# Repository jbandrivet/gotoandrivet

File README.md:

# GotoAndrivet — Contrôleur Multi-Montures OnStep

**Site du projet : [goto-andrivet.duckdns.org](https://goto-andrivet.duckdns.org)**

**Fonctionne sous Linux et sous Windows** : [installation Linux](#installation-en-un-clic-linux) ·
[installation Windows](#installation-windows). La monture et ses firmwares sont les mêmes : une carte
flashée une fois sert avec les deux.

Ce projet supporte de manière universelle trois types de montures astronomiques :
1. **Alt-Azimutale (AltAz)** : Pour montures Dobson et Alt-Azimutales standards.
2. **Fourche Équatoriale (ForkEq)** : Pour montures équatoriales à fourche ou tables équatoriales (aucun retournement de méridien requis, suivi sidéral direct sur l'angle horaire).
3. **Monture Équatoriale Allemande (GermanEq / GEM)** : Pour montures équatoriales allemandes (gestion automatique du **retournement de méridien** et de la position de pilier *Pier Side* Est/Ouest).

---

## Installation en un clic (Linux)

La carte du ciel et GoTo (**GotoAndrivet**) et le **configurateur** s'installent ensemble, avec leurs raccourcis sur le Bureau et dans le menu des applications. L'installateur prend toujours la dernière version du dépôt ; ensuite, le bouton « Mise à jour » des applications suffit.

**Ubuntu et Debian, le plus simple : [⬇ Télécharger GotoAndrivet.deb](https://github.com/jbandrivet/gotoandrivet/releases/latest/download/GotoAndrivet.deb)**

1. Double-cliquez sur le fichier téléchargé : le Centre d'applications s'ouvre. Cliquez sur **Installer** (votre mot de passe est demandé).
2. Ouvrez **GotoAndrivet - Carte du ciel** depuis le menu des applications. La première fois, GotoAndrivet s'installe dans votre dossier personnel (quelques minutes), puis s'ouvre.

**Autres distributions : [⬇ Télécharger l'installateur Linux](https://github.com/jbandrivet/gotoandrivet/releases/latest/download/Install_Goto_Universal)**, puis, dans le dossier Téléchargements :

1. clic droit sur `Install_Goto_Universal` → **Propriétés** → activez **Exécutable comme programme** ;
2. clic droit → **Exécuter comme un programme**, puis « Installer ».

Le double-clic ne lance pas un programme téléchargé : il propose de chercher une application dans le Centre d'applications, qui ne trouve rien. Passez par le clic droit.

Ou en une seule commande, dans un terminal :

```sh
wget -qO- https://raw.githubusercontent.com/jbandrivet/gotoandrivet/main/installer.sh | sh
```

Prérequis pour l'installateur et la commande (le paquet .deb les installe tout seul) : `sudo apt install python3-venv python3-tk`. Pour le module caméra : `sudo apt install astrometry.net astrometry-data-tycho2` et le SDK caméra de ZWO.

**Connexion de la monture** : dans la carte du ciel, laissez le port sur **Auto** et cliquez sur **Connecter**. La carte du ciel essaie d'abord le dernier port qui a marché, puis les cartes Teensy et Arduino, puis les adaptateurs série USB (CH340, FTDI, CP210x, PL2303), et garde celui où la monture répond. Les ports déjà pris (KStars, dérotateur) sont sautés. Si la recherche ne trouve rien, choisissez le port dans la liste, ou tapez-le, par exemple `/dev/ttyACM0`.

---

## Installation (Windows)

Trois `.exe` autonomes, sans installation : copiez-les dans un dossier à vous (Documents, Bureau) et
double-cliquez.

* **[⬇ GotoAndrivet_Carte_du_ciel.exe](https://github.com/jbandrivet/gotoandrivet/releases/download/windows/GotoAndrivet_Carte_du_ciel.exe)** : la carte du ciel et le GoTo
* **[⬇ GotoAndrivet_Configurateur.exe](https://github.com/jbandrivet/gotoandrivet/releases/download/windows/GotoAndrivet_Configurateur.exe)** : le réglage de la monture
* **[⬇ GotoAndrivet_Raquette.exe](https://github.com/jbandrivet/gotoandrivet/releases/download/windows/GotoAndrivet_Raquette.exe)** : la raquette virtuelle

La monture (Arduino Mega, clone ou Teensy) est trouvée toute seule sur son port COM. Si Windows affiche
« Windows a protégé votre ordinateur » : **Informations complémentaires** → **Exécuter quand même** (les
`.exe` ne sont pas signés).

Les `.exe` sont fabriqués par GitHub à chaque modification du programme
([release `windows`](https://github.com/jbandrivet/gotoandrivet/releases/tag/windows)) ; le bouton
« Mise à jour » passe au rouge quand une nouvelle version existe et les remplace d'un clic. Pas
disponibles sous Windows : caméras ZWO, focuseur EAF, astrométrie et guidage. Fabrication : dossier
[`windows/`](windows/LISEZMOI.txt).

## Structure du Projet

* **`goto_andrivet.py`** : L'application principale en Python (interface graphique Tkinter avec carte du ciel interactive : étoiles, constellations, Soleil, Lune et planètes, catalogues Messier/NGC/IC/Caldwell, dérotateur et mise à jour en ligne).
* **`photo.py`** : Le module caméra de la carte du ciel (caméra ZWO ou simulée, photos FITS, astrométrie locale avec solve-field, correction après GoTo, modèle de pointage, angle de cadrage).
* **`guidage.py`** : Le module de guidage de la carte du ciel (deuxième caméra ZWO ou simulée, calibration automatique, corrections envoyées par le PC à la monture, courbe des erreurs, dithering entre les poses).
* **`goto_andrivet_config_tool.py`** : L'utilitaire de configuration en style Windows 95 permettant de régler les coordonnées, vitesses, rapports d'engrenage et de flasher le firmware.
* **`raquette_virtuelle.py`** : L'émulateur de la raquette Teensy pour piloter le télescope depuis l'ordinateur.
* **`ciel_donnees.py`** : Les données de la carte du ciel : étoiles du Yale Bright Star Catalogue jusqu'à la magnitude 6,5, lignes et noms des 88 constellations (Stellarium, CC BY-SA 4.0), objets Messier, Caldwell, NGC et IC (OpenNGC, CC BY-SA 4.0). Fichier généré par `outils/generer_ciel_donnees.py` : ne pas le modifier à la main.
* **`mise_a_jour.py`** : La mise à jour en ligne depuis GitHub, commune à la carte du ciel et à l'utilitaire de configuration.
* **`outils/`** : Le générateur de `ciel_donnees.py` (il télécharge les catalogues auprès du CDS, de Stellarium et d'OpenNGC).
* **`mega_monture/`** : Le firmware classique (1 étoile) pour le contrôleur Arduino Mega 2560.
* **`teensy_monture/`** : Le nouveau firmware haute performance pour contrôleur Teensy 4.1 (inclut le modèle de pointage : défauts de la monture calculés sur 50 étoiles au plus).
* **`teensy_raquette/`** : Le firmware C++ pour la raquette physique avec écran LCD (sur Teensy 4.1).

---

## Guide d'Installation & Mode d'Emploi

### 1. Prérequis
Pour exécuter les applications graphiques en Python sur votre ordinateur, vous devez disposer de **Python 3**, du module **Tkinter** et de la bibliothèque **pyserial**. La bibliothèque **ephem** est facultative : elle affiche le Soleil, la Lune et les planètes sur la carte du ciel.

Sur Ubuntu / Debian / Raspberry Pi OS, installez-les via votre terminal :
```bash
sudo apt update
sudo apt install python3 python3-tk python3-pip
pip3 install pyserial ephem
```

### 2. Démarrage des Applications
Exécutez les scripts Python correspondants depuis le dossier du projet :

* **Configuration & Flashage** :
  ```bash
  python3 goto_andrivet_config_tool.py
  ```
* **Cartographie du Ciel & Pilotage** :
  ```bash
  python3 goto_andrivet.py
  ```
* **Raquette Virtuelle (Émulateur)** :
  ```bash
  python3 raquette_virtuelle.py
  ```

### 3. Compiler & Flasher sans IDE Arduino
Vous pouvez programmer vos cartes directement depuis l'utilitaire de configuration (sans avoir besoin d'ouvrir l'IDE Arduino classique) :
1. Installez l'utilitaire [arduino-cli](https://arduino.github.io/arduino-cli/latest/) sur votre PC.
2. Ouvrez l'utilitaire de configuration (`python3 goto_andrivet_config_tool.py`).
3. Sélectionnez le **Port** série de votre carte dans les paramètres de connexion.
4. Dans l'encadré **« Téléversement du Firmware »**, cliquez sur le bouton correspondant à votre carte pour compiler et flasher automatiquement.

### 4. Schéma de Câblage Rapide (Monture : Mega ou Teensy)

Câblez votre contrôleur principal en suivant ce schéma (les broches sont identiques pour le Mega et le Teensy, à l'exception du Buzzer, de l'`ENB` du focuseur et du GPS, dont les fils TX/RX sont croisés d'une carte à l'autre) :

| Composant / Axe | Broche Arduino Mega 2560 | Broche Teensy 4.1 | Signal Module / Driver |
| :--- | :--- | :--- | :--- |
| **Moteur Azimut (AZ/RA)** | **Pin 2** | **Pin 2** | `PUL+` (Pulse/Step) |
| | **Pin 3** | **Pin 3** | `DIR+` (Direction) |
| | **Pin 4** | **Pin 4** | `ENB+` (Enable) |
| **Moteur Altitude (ALT/DEC)** | **Pin 5** | **Pin 5** | `PUL+` (Pulse/Step) |
| | **Pin 6** | **Pin 6** | `DIR+` (Direction) |
| | **Pin 7** | **Pin 7** | `ENB+` (Enable) |
| **Moteur Dérotateur** | **Pin 8** | **Pin 8** | `PUL+` (Pulse/Step) |
| | **Pin 9** | **Pin 9** | `DIR+` (Direction) |
| | **Pin 10** | **Pin 10** | `ENB+` (Enable) |
| **Moteur Focuseur** | **Pin 11** | **Pin 11** | `PUL+` (Pulse/Step) |
| | **Pin 12** | **Pin 12** | `DIR+` (Direction) |
| | **Pin 13** | **Pin 21** | `ENB+` (Enable) |
| **Buzzer** | **Pin 49** | **Pin 20** | Mega : borne `+` en direct (buzzer actif). Teensy : par un transistor (voir § 6) |
| **Port Série PC** | **Non dispo** | **Pin 25 (RX6)** | `TX` de l'adaptateur USB/Série TTL (Câble long) |
| | **Non dispo** | **Pin 24 (TX6)** | `RX` de l'adaptateur USB/Série TTL |
| **Raquette Teensy** | **Pin 15 (RX3)** | **Pin 15 (RX3)** | `TX` de la raquette Teensy |
| | **Pin 14 (TX3)** | **Pin 14 (TX3)** | `RX` de la raquette Teensy |
| **Module GPS** | **Pin 17 (RX2)** | **Pin 16 (RX4)** | `TX` du module GPS |
| | **Pin 16 (TX2)** | **Pin 17 (TX4)** | `RX` du module GPS |
| **Drivers TMC5160 (SPI1, PCB)** | **Non dispo** | **Pin 26 (MOSI1)** | `SDI` des modules (ponts SPI fermés) |
| | **Non dispo** | **Pin 27 (SCK1)** | `SCK` des modules |
| | **Non dispo** | **Pin 39 (MISO1)** | `SDO` des modules |
| | **Non dispo** | **Pins 41 / 40 / 38 / 37** | `CSN` AZ / ALT / Dérotateur / Focuseur |

*Note : Les signaux de masse négatifs (`PUL-`, `DIR-`, `ENB-` des drivers, GND du buzzer, du GPS et de la Teensy) doivent tous être connectés à une broche **GND** de votre carte.*
*(Consultez le fichier `fiche_technique.md` pour des explications approfondies).*

### 4.1 Schéma de Câblage de la Raquette (Teensy 4.1)

Si vous fabriquez la raquette physique avec un Teensy 4.1, voici le câblage à effectuer :

| Composant | Broche Teensy 4.1 | Connexion / Signal |
| :--- | :--- | :--- |
| **Écran LCD (I2C)** | **Pin 18 (SDA0)** | `SDA` de l'écran LCD |
| | **Pin 19 (SCL0)** | `SCL` de l'écran LCD |
| | **VIN** | `VCC` (5V) de l'écran LCD |
| | **GND** | `GND` de l'écran LCD |
| **Boutons Poussoirs** | **Pin 6** | Bouton **Haut (UP)** (vers GND) |
| | **Pin 7** | Bouton **Bas (DOWN)** (vers GND) |
| | **Pin 8** | Bouton **Gauche (LEFT)** (vers GND) |
| | **Pin 9** | Bouton **Droite (RIGHT)** (vers GND) |
| | **Pin 10** | Bouton **Validation (ENTER)** (vers GND) |
| **Câble RJ11 (vers Mega)**| **GND** | Pin 1 RJ11 (`GND` de la Monture) |
| | **VIN** | Pin 2 RJ11 (`VIN` / `5V` de la Monture) |
| | **Pin 1 (TX1)** | Pin 3 RJ11 (vers `RX3` Pin 15 Monture) |
| | **Pin 0 (RX1)** | Pin 4 RJ11 (vers `TX3` Pin 14 Monture) |

*ATTENTION : Le Teensy est alimenté par la pin 5V du Mega via VIN. Ne pas brancher l'USB du Teensy en même temps, sauf si le pad VUSB a été coupé au préalable.*

### 5. Arduino Mega 2560 vs Teensy 4.1 (Contrôleur de Monture)

Le projet vous permet de choisir le cerveau principal de la monture. Bien que le câblage soit quasiment identique, voici les différences pour vous aider à choisir :

| Caractéristique | Arduino Mega 2560 | Teensy 4.1 |
| :--- | :--- | :--- |
| **Vitesse de calcul** | 16 MHz (8-bit) | **600 MHz** (32-bit ARM) |
| **Précision (Maths)** | Flottants 32-bit lents | **Flottants 64-bit (double)** natifs ultra-rapides |
| **Microstepping & Vitesse max**| Limité (saturera à très haut microstepping) | **Parfait** (génère des impulsions à plus de 200kHz sans sourciller) |
| **Modèle de pointage** | Synchro à une étoile | **Défauts de la monture** calculés sur 50 étoiles au plus |
| **PEC (erreur périodique de la vis)** | Non | **Oui** (équatoriales) |
| **Evolutivité (Futur)** | Faible | **Très haute** (Port USB Host pour Manette/Gamepad) |
| **Coût** | ~15-20€ (Clones pas chers) | ~35-40€ |

**Recommandation** : Si vous utilisez de petits drivers (1/16 ou 1/32 de pas) et voulez un système économique, le **Mega 2560** fait parfaitement le travail. Si vous utilisez des drivers modernes (TMC2209, M542) à fort microstepping (1/128, 1/256), que vous voulez des déplacements GoTo ultra-rapides et silencieux, et le modèle de pointage multi-étoiles intégré, optez sans hésiter pour le **Teensy 4.1**.

### 6. Matériel Compatible

Pour monter votre système GotoAndrivet, les composants matériels suivants sont compatibles et recommandés :

* **Cartes de Contrôle** :
  * **Arduino Mega 2560** ou **Teensy 4.1** (au choix pour la carte principale de la monture).
  * **Teensy 4.1** (pour la raquette de commande physique - *Optionnelle*).
* **Drivers de Moteurs** :
  * Drivers standard acceptant des entrées `PUL/DIR` (Impulsion/Direction) comme les modèles **M542**, **DM542**, **TB6600**, **TMC2209**, etc.
  * Deux PCB monture (Teensy) au choix : une carte à modules StepStick, dont le **BTT TMC5160 Pro** configuré en SPI, et une carte pour drivers externes (voir *Cartes Monture* plus bas).
* **Moteurs** :
  * Moteurs pas à pas bipolaires (ex. **NEMA 17** ou **NEMA 23** en 200 pas/tour).
* **Module GPS (Optionnel)** :
  * Module **Adafruit Ultimate GPS** (MTK3339) ou tout autre récepteur GPS délivrant des trames NMEA standards à 9600 bauds sur port série.
* **Afficheur Raquette** :
  * Écran **LCD 20x4** caractères équipé d'un adaptateur **I2C** (généralement à l'adresse `0x27`).
* **Boutons Raquette** :
  * 5 boutons poussoirs momentanés (Haut, Bas, Gauche, Droite, Validation).
* **Alerte Sonore** :
  * Un **Buzzer actif 5V** ou un **Buzzer passif**. Sur le Mega, un buzzer actif se câble directement. Sur le Teensy, passez par un transistor : une broche ne fournit que quelques mA, et un buzzer passif en tire 80 à 200. Un NPN (PN2222A) avec 1 kΩ sur la base, le buzzer entre le 5V et le collecteur, en série avec 68 Ω, et une diode 1N4148 à ses bornes : c'est le montage des cartes.

*Note concernant la raquette physique : La construction de la raquette matérielle (carte Teensy, écran LCD et boutons) n'est **pas obligatoire**. Si vous utilisez la monture en mode "remote", ou que vous la pilotez exclusivement depuis un PC, un planétarium, ou un boîtier type ASIAIR, l'Arduino Mega suffit à lui seul pour tout gérer via la connexion USB.*

---

## Fonctionnalités Avancées

* **Modèle de pointage (Teensy Monture uniquement)** : à partir de 50 étoiles de synchro au plus, la carte calcule les défauts de la monture (décalage des axes, mise en station, tube pas d'équerre, axes pas perpendiculaires, flexion du tube et de la fourche, roues décentrées), puis interpole ce qui reste pour tomber juste sur chaque étoile. Une synchro sur la mauvaise étoile est refusée (refaite, elle est acceptée et le modèle repart de zéro) ; la dernière étoile se retire (`:CMU#`). L'onglet *Précision* de la carte du ciel et la raquette affichent le nombre d'étoiles, l'erreur restante et l'erreur de mise en station. Le modèle est gardé en mémoire d'une soirée à l'autre si la monture est éteinte parquée. Remise à zéro par `:CML#`. Détails : fiche technique, § 5.
* **PEC (Teensy Monture, équatoriales)** : l'erreur périodique de la vis s'enregistre pendant un tour de vis guidé, puis se corrige d'avance (commandes OnStep, onglet *PEC* d'Ekos compris). Il faut indiquer le nombre de dents de la roue AD dans le configurateur.
* **Suivi de la Lune et du Soleil calculé** (les deux cartes) : position de l'astre recalculée en continu, en ascension droite et en déclinaison.
* **Compatible INDI et ASCOM** (les deux cartes) : testé le 18/11/2026 avec un vrai Teensy, sous Linux avec le pilote INDI *LX200 OnStep* (Ekos) et sous Windows avec NINA et le pilote *ASCOM OnStep* : GoTo des deux côtés du pilier, guidage, synchronisation, Lune/Soleil/sidéral, jeu, arrêt, parking.
* **Réfraction corrigée** (les deux cartes) : au GoTo et au suivi, réglable depuis Ekos (*Compensation*, `:To#` / `:Tn#`). Sur la Teensy, avec la température et la pression du lieu (`:SX9A` / `:SX9B`, envoyées par la carte du ciel et par Ekos).
* **GoTo anticipé** (les deux cartes) : la carte vise l'endroit où sera l'objet à l'arrivée.
* **Ajout du type de monture `GermanEq`** : Le firmware de l'Arduino Mega calcule automatiquement les inversions d'axes (Ascension Droite et Déclinaison) lors du franchissement du méridien.
* **Commande standard `:Gm#` implémentée** : Renvoie le *Pier Side* (`E#` pour l'Est, `W#` pour l'Ouest, `N#` pour les autres modes) requis pour les logiciels de guidage comme Ekos/INDI.
* **Commande standard `:D#` implémentée** : Permet l'interrogation dynamique du statut de pointage (Slewing), accélérant drastiquement le modèle de pointage automatique ZWO en évitant les pauses fixes.
* **Intégration complète dans les interfaces** : Le sélecteur de monture dans `goto_andrivet_config_tool.py`, `goto_andrivet.py` et la raquette physique Teensy supporte désormais les trois options distinctes (`AltAz`, `ForkEq`, `GermanEq`).

---

## Licence

Ce projet est sous licence **GNU GPL v3**. Consultez le fichier [LICENSE](LICENSE) pour plus de détails.

## Cartes Monture (PCB 36V / 12V)

Il existe deux cartes monture, au choix selon les drivers utilisés. Elles ont les mêmes dimensions (150 × 110 mm), les mêmes fixations, les mêmes connecteurs d'alimentation, de raquette, de GPS et de PC, et le même câblage du Teensy : le firmware est identique.

| Carte | Dossier | Drivers | Boîtier |
|---|---|---|---|
| **StepStick** | `pcb/monture/` | 4 modules au format StepStick sur la carte (A4988, DRV8825, TMC2208/2209, TMC5160 en SPI) | `boitier_monture.scad`, 45 mm de haut |
| **Drivers externes** | `pcb/monture_ext/` | 4 drivers externes (DM542, DM556, TB6600…), signaux 5 V et alimentation par axe | `boitier_monture_ext.scad`, 35 mm de haut |

Sans PCB, câblez vous-même le Mega ou le Teensy en suivant le plan de câblage de la section 4. Dans l'outil de configuration, indiquez votre choix sur la ligne **« Câblage monture »** (PCB StepStick, PCB drivers externes ou câblage manuel). Avec un PCB, l'outil impose le Teensy 4.1, et la section TMC5160 n'est active qu'avec la carte StepStick. Le bouton **« Plan de câblage »** affiche les broches de la carte choisie et les connecteurs du PCB.

### Commun aux deux cartes
- **Alimentation** : un seul bus moteur, alimenté soit par le **bornier 36V**, soit par la **prise jack 12V**. Chaque entrée passe par une des deux diodes Schottky de `D_IN` (MBR20100CT, cathode commune) : des fils inversés ou un jack à centre négatif ne passent pas, et le 36V du bornier ne remonte pas dans le bloc 12V. Vient ensuite le fusible `F_IN` (TR5 temporisé 4 A, sur support), commun aux deux entrées. Toute la carte et tous les drivers reçoivent la tension de l'entrée branchée, moins environ 0,5 V.
  - En 36V, n'utilisez pas d'A4988 (35 V max) ni de TMC2208/TMC2209 (29 V max) : pour ces petits drivers, alimentez la carte uniquement par le jack 12V.
- Le buck LM2596HV (jusqu'à 60 V en entrée) fabrique le 5V à partir de 12V comme de 36V.
- Des résistances de rappel (`RN_EN`) maintiennent EN à l'état haut tant que le Teensy n'a pas démarré : les drivers restent désactivés à la mise sous tension.
- Le Teensy 4.1 de la monture n'a pas de port USB Host câblé.
- Sur le Teensy de la monture, **coupez le pont VUSB-VIN** sous la carte : le Teensy est alimenté par le 5V du PCB (VIN) et reste branché en USB au PC.
- Port **PC SERIAL** (Serial6, broches 24/25) : les repères RX/TX sont donnés côté Teensy (`3 TX6`, `4 RX6`). Il faut donc les croiser vers l'adaptateur, et ne pas brancher son 5V sur la broche `2 +5V`. L'adaptateur USB-série doit travailler en **3,3 V** : un adaptateur 5 V enverrait 5 V sur `RX6`, que le Teensy ne supporte pas.
- Le buzzer est commandé par un transistor (`Q_BUZ`, PN2222A) et alimenté en 5V à travers 68 Ω, avec une diode 1N4148 à ses bornes : un buzzer actif 5V ou un buzzer passif conviennent.

### Carte StepStick (`pcb/monture/`)
- Chaque axe a un support au format **StepStick / Pololu** (2 × 8 broches espacées de 12,7 mm), piloté directement par le Teensy, et un bornier moteur à 4 points (bobine 1 : 1B/1A, bobine 2 : 2A/2B).
- Orientation d'un module StepStick : sa broche **EN** va sur la pastille marquée `EN` (en haut à gauche). **VMOT** se trouve donc en face, sur la pastille marquée `VM`. La logique des modules (VIO) est alimentée en **3,3 V**.
- **Ponts SPI (TMC5160)** : sous chaque support, entre les deux rangées, se trouvent 5 ponts à souder marqués `SPI`. Ils sont en face des broches 2 à 6 du module. De haut en bas : `SDI` vers MOSI1 (broche 26), `SCK` vers SCK1 (27), `CSN` vers le CS de l'axe (41 AZ, 40 ALT, 38 dérotateur, 37 focuseur), `SDO` vers MISO1 (39), et `CLK` vers GND (horloge interne du TMC5160).
  - **Ponts ouverts** (réglage par défaut) : le support accepte les modules STEP/DIR sans SPI, c'est-à-dire TMC2208/TMC2209 en mode autonome, A4988 ou DRV8825.
    - **A4988 et DRV8825 : reliez RESET à SLEEP sur le module** (petit fil ou goutte d'étain entre les deux broches voisines). Le PCB laisse ces broches en l'air : sans ce pont, l'A4988 a un RESET flottant, et le DRV8825, dont RESET a un rappel interne au niveau bas, ne bouge pas du tout.
    - **Micro-pas** : le PCB ne câble pas les broches MS1 à MS3. Elles restent au niveau bas, ce qui donne le pas entier sur un A4988 ou un DRV8825 et 1/8 de pas sur un TMC2208/TMC2209. Pour une autre valeur, reliez les broches MSx voulues à la broche VIO du support (3,3 V) par un fil soudé sur le module, d'après sa table de micro-pas. Le réglage *Microstepping* de l'outil de configuration doit toujours être égal aux micro-pas du module (1, 8, 16…).
  - **Les 5 ponts fermés** (une goutte d'étain chacun) : pour un **BTT TMC5160 Pro**, ou un autre TMC5160 au format StepStick avec le même brochage (EN, SDI, SCK, CSN, SDO, CLK, STEP, DIR).
  - Ne fermez jamais les ponts avec un A4988, un DRV8825 ou un TMC2209 : leurs broches MSx, RESET et SLEEP se retrouveraient sur le bus SPI.
- **Configuration des TMC5160 (firmware Teensy)** : au démarrage, puis chaque seconde, le firmware cherche un TMC5160 sur chaque axe et le configure (courant, micro-pas, stealthChop). Un TMC5160 en SPI garde son étage de puissance coupé tant qu'il n'est pas configuré. Si le 36V n'est pas encore là, le module ne répond pas : il est configuré dès que le 36V arrive, et reconfiguré après une coupure.
  - Micro-pas : AZ/ALT utilisent le réglage *Microstepping*, qui doit être une puissance de 2 (16, 32, 64, 128 ou 256). Une valeur comme 125 est refusée et l'axe reste coupé (état `M`). Le dérotateur et le focuseur sont à 16 micro-pas par défaut : ajustez les *Pas/Deg* du dérotateur en conséquence.
  - Courant : il se règle dans l'outil de configuration, de 100 à 3000 mA RMS par axe (Rsense 0,075 Ω du BTT TMC5160 Pro), avec un courant de maintien en %. Valeurs par défaut : 800 mA pour AZ/ALT, 400 mA pour le dérotateur et le focuseur, maintien à 50 %.
  - Commandes : `:XFS0#` / `:XFS1#` (désactiver / activer, activé par défaut), `:XTS#` (état par axe : `-` SPI désactivé, `0` absent, `1` configuré, `M` micro-pas refusé, `E` défaut driver), `:XTI<a|e|d|f>[mA]#` (courant), `:XTH[%]#` (maintien), `:XTP[0|1]#` (stealthChop), `:XTMd[n]#` / `:XTMf[n]#` (micro-pas dérotateur / focuseur), `:XTC#` (tout reconfigurer). Sans valeur, ces commandes renvoient le réglage en cours.
  - Le firmware Mega n'a pas de SPI : le PCB est prévu pour le Teensy.
  - Hauteur : un TMC5160 avec radiateur est plus haut qu'un StepStick ordinaire. Le boîtier fait donc 45 mm de haut (`box_h` dans `boitier_monture.scad`), ce qui laisse 25,8 mm entre la carte du module et le couvercle. Un BTT TMC5160 Pro (23,2 mm hors tout) passe avec au moins 4 mm de marge, et les grilles du couvercle se trouvent au-dessus des radiateurs.

### Carte drivers externes (`pcb/monture_ext/`)
- Chaque axe a deux borniers sur le bord haut :
  - **`J_VM`** (5,08 mm, fil de 1,5 mm²) : `VM` et `GND`, l'alimentation du driver. `VM` est le bus moteur, donc 36V ou 12V selon l'entrée branchée. Chaque sortie a son condensateur de 220 µF.
  - **`J_SIG`** (3,5 mm) : `EN`, `STEP`, `DIR`, `GND`, en 5 V. Les signaux du Teensy passent par trois 74ACT125, toujours actifs.
- Câblage d'un DM542 (cathode commune) : `STEP` → `PUL+`, `DIR` → `DIR+`, `EN` → `ENA+`, et `GND` → `PUL−`, `DIR−` et `ENA−` reliés ensemble. Le moteur se branche sur le driver. Avec `ENA` câblé, le driver relâche le moteur au parking ; sinon, le moteur reste alimenté en permanence.
- Un plan de cuivre GND (face dessous) et un plan +36V (face dessus, de l'entrée jusqu'aux borniers `J_VM`) portent le courant des drivers.
- Réglages : le *Microstepping* de l'outil de configuration doit être égal au nombre de pas par tour réglé sur le driver divisé par 200 (par exemple 128 pour 25 600 pas/tour). Toutes les valeurs sont acceptées, puissances de 2 ou non. AZ et ALT partagent ce réglage : réglez leurs deux drivers pareil.
- Vitesse de GoTo : le DM542 accepte 200 kHz au plus, avec des impulsions d'au moins 2,5 µs. Restez sous environ 150 kHz, soit une vitesse maximale d'environ 150 000 divisé par le nombre de pas par degré (environ 2,8°/s à 25 600 pas/tour avec une réduction de 750:1).
- Cette carte n'a pas de bus SPI : dans l'outil de configuration, l'état TMC5160 des axes est « absent », ce qui est normal. On peut décocher « Drivers TMC5160 ».

## Mise en station robotisée (`pcb/mise_en_station/`, `mise_en_station/`)

Carte facultative, à part, pour les montures équatoriales (`ForkEq`, `GermanEq`) : deux moteurs pas à pas tournent les vis de réglage de la monture, l'une en azimut, l'autre en hauteur. La caméra mesure l'erreur au pôle, et le PC fait tourner les vis jusqu'à ce qu'elle passe sous la tolérance.

- **Carte** (110 x 85 mm, 2 couches, dessinée par `pcb/build_kicad_pcbs.py`, puis routée avec Freerouting par le MCP KiCad) : un **Arduino Nano** branché en USB sur le PC, 2 supports StepStick (**TMC2209** conseillé, A4988 ou DRV8825 possibles), une entrée **12 V** par jack (fusible T2A, diode 1N5822 contre l'inversion), 2 borniers moteurs, 2 borniers de fins de course (MIN, MAX, GND ; contact vers GND), une prise I2C pour plus tard, un voyant ACTIF et la mesure du 12 V.
  - Ponts à souder sous chaque module : `MS1` et `MS2` vers le 5 V (micro-pas) ; `RS` relie RESET à SLEEP, **à fermer pour un A4988 ou un DRV8825, à laisser ouvert pour un TMC2209**.
  - Sans le 12 V, le Nano reste alimenté par l'USB mais refuse de bouger les moteurs (le voyant clignote).
- **Boîtier** `pcb/mise_en_station/boitier_mise_en_station.scad` (OpenSCAD, 118 x 119,5 x 42,5 mm) : base et couvercle à imprimer, 4 presse-étoupes PG7 (2 moteurs, 2 fins de course) et une pastille à percer pour le câble I2C, jack et USB accessibles de l'extérieur, couvercle aéré au-dessus des drivers avec un trou pour le voyant, 4 pattes à lumière pour vis M5. `sh pcb/mise_en_station/verifier_boitier.sh` contrôle qu'aucune pièce ne touche le boîtier et refait les STL.
- **Firmware** `mise_en_station/mise_en_station.ino` (Nano, 38400 bauds) : se flashe depuis l'outil de configuration (« Arduino Nano (Mise en station) » ; l'ancien chargeur de démarrage des clones est essayé si besoin). Mouvements en pas avec rampe, rattrapage du jeu (la vis arrive toujours sur sa cible dans le même sens), arrêt sur fin de course et sur perte du 12 V, réglages gardés en EEPROM. Les commandes sont décrites en tête du fichier.
- **Logiciel** : onglet **Mise en station** du module Caméra de la carte du ciel (`photo.py`, calculs dans `mise_en_station_robot.py`).
  1. Visez vers le méridien, entre 30° et 70° de hauteur, et cliquez « Mesurer l'axe » : 3 images, en ne tournant que l'axe d'AD (de 30° par défaut), donnent l'axe de la monture. Le suivi peut rester en marche.
  2. « Correction automatique » : au premier usage, chaque moteur fait un petit mouvement pour la calibration (pas par minute d'arc, gardée ensuite). Puis les deux moteurs corrigent, une image mesure ce que la monture a vraiment fait, et la boucle continue. Sous la tolérance, l'axe est re-mesuré par 3 images pour vérifier.
  - Sans carte, « Mesurer l'erreur » sert à régler les vis à la main : chaque image dit de combien tourner, et dans quel sens.
  - Option « pôle relevé par la réfraction », pour une monture qui suit sans corriger la réfraction.
- **Essai sans matériel** : `python3 mise_en_station/essai_mise_en_station.py` fait tourner le firmware dans un émulateur PC (`mise_en_station/emulateur/`) face à une monture simulée (vis avec du jeu, charnière imparfaite, suivi, Nord et Sud).

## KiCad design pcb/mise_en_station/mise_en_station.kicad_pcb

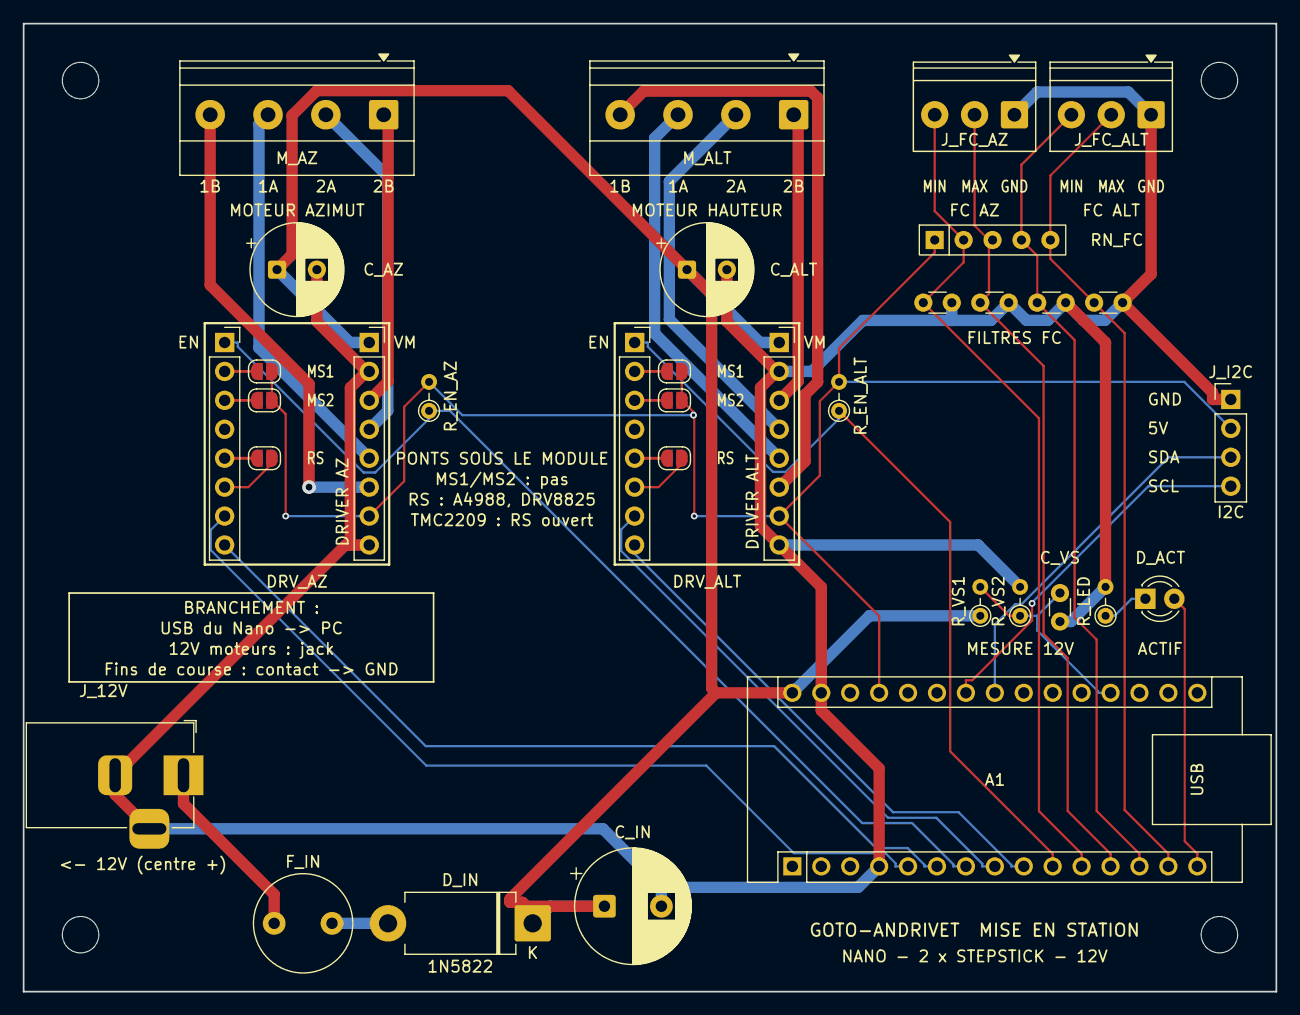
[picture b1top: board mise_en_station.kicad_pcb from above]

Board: 2 copper layers, 110.0 x 85.0 mm, 38 parts (0 on the bottom side), 36 nets.

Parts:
A1: Arduino Nano; Arduino_Nano
C_ALT: 100uF 35V; CP_Radial_D8.0mm_P3.50mm
C_AZ: 100uF 35V; CP_Radial_D8.0mm_P3.50mm
C_FC1, C_FC2, C_FC3, C_FC4: 100nF; C_Disc_D3.0mm_W1.6mm_P2.50mm
C_IN: 470uF 35V; CP_Radial_D10.0mm_P5.00mm
C_VS: 100nF; C_Disc_D3.0mm_W1.6mm_P2.50mm
DRV_ALT_L: Logique; PinSocket_1x08_P2.54mm_Vertical
DRV_ALT_R: Puissance; PinSocket_1x08_P2.54mm_Vertical
DRV_AZ_L: Logique; PinSocket_1x08_P2.54mm_Vertical
DRV_AZ_R: Puissance; PinSocket_1x08_P2.54mm_Vertical
D_ACT: LED verte 3 mm; LED_D3.0mm
D_IN: 1N5822; D_DO-201AD_P12.70mm_Horizontal
F_IN: T2A; Fuse_Littelfuse_372_D8.50mm
H1, H2, H3, H4: M3 Fixation; MountingHole_3.2mm_M3
JP_ALT_MS1: MS1; SolderJumper-2_P1.3mm_Open_RoundedPad1.0x1.5mm
JP_ALT_MS2: MS2; SolderJumper-2_P1.3mm_Open_RoundedPad1.0x1.5mm
JP_ALT_RS: RS; SolderJumper-2_P1.3mm_Open_RoundedPad1.0x1.5mm
JP_AZ_MS1: MS1; SolderJumper-2_P1.3mm_Open_RoundedPad1.0x1.5mm
JP_AZ_MS2: MS2; SolderJumper-2_P1.3mm_Open_RoundedPad1.0x1.5mm
JP_AZ_RS: RS; SolderJumper-2_P1.3mm_Open_RoundedPad1.0x1.5mm
J_12V: 12V Jack; BarrelJack_Horizontal
J_FC_ALT: FC ALT; TerminalBlock_Phoenix_PT-1,5-3-3.5-H_1x03_P3.50mm_Horizontal
J_FC_AZ: FC AZ; TerminalBlock_Phoenix_PT-1,5-3-3.5-H_1x03_P3.50mm_Horizontal
J_I2C: I2C; PinHeader_1x04_P2.54mm_Vertical
M_ALT: MOTEUR ALT; TerminalBlock_Phoenix_MKDS-1,5-4-5.08_1x04_P5.08mm_Horizont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
M_AZ: MOTEUR AZ; TerminalBlock_Phoenix_MKDS-1,5-4-5.08_1x04_P5.08mm_Horizont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
RN_FC: 10k x4 (commun broche 1); R_Array_SIP5
R_EN_ALT: 10k; R_Axial_DIN0204_L3.6mm_D1.6mm_P2.54mm_Vertical
R_EN_AZ: 10k; R_Axial_DIN0204_L3.6mm_D1.6mm_P2.54mm_Vertical
R_LED: 1k; R_Axial_DIN0204_L3.6mm_D1.6mm_P2.54mm_Vertical
R_VS1: 47k; R_Axial_DIN0204_L3.6mm_D1.6mm_P2.54mm_Vertical
R_VS2: 10k; R_Axial_DIN0204_L3.6mm_D1.6mm_P2.54mm_Vertical

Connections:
+5V: A1.27, DRV_ALT_R.7, DRV_AZ_R.7, JP_ALT_MS1.2, JP_ALT_MS2.2, JP_AZ_MS1.2, JP_AZ_MS2.2, J_I2C.2, RN_FC.1, R_EN_ALT.2, R_EN_AZ.2
ALT_1A: DRV_ALT_R.5, M_ALT.3
ALT_1B: DRV_ALT_R.6, M_ALT.4
ALT_2A: DRV_ALT_R.4, M_ALT.2
ALT_2B: DRV_ALT_R.3, M_ALT.1
ALT_DIR: A1.9, DRV_ALT_L.8
ALT_EN: A1.10, DRV_ALT_L.1, R_EN_ALT.1
ALT_MS1: DRV_ALT_L.2, JP_ALT_MS1.1
ALT_MS2: DRV_ALT_L.3, JP_ALT_MS2.1
ALT_RST: DRV_ALT_L.5, JP_ALT_RS.1
ALT_SLP: DRV_ALT_L.6, JP_ALT_RS.2
ALT_STEP: A1.8, DRV_ALT_L.7
AZ_1A: DRV_AZ_R.5, M_AZ.3
AZ_1B: DRV_AZ_R.6, M_AZ.4
AZ_2A: DRV_AZ_R.4, M_AZ.2
AZ_2B: DRV_AZ_R.3, M_AZ.1
AZ_DIR: A1.6, DRV_AZ_L.8
AZ_EN: A1.7, DRV_AZ_L.1, R_EN_AZ.1
AZ_MS1: DRV_AZ_L.2, JP_AZ_MS1.1
AZ_MS2: DRV_AZ_L.3, JP_AZ_MS2.1
AZ_RST: DRV_AZ_L.5, JP_AZ_RS.1
AZ_SLP: DRV_AZ_L.6, JP_AZ_RS.2
AZ_STEP: A1.5, DRV_AZ_L.7
FC_ALT_MAX: A1.14, C_FC4.1, J_FC_ALT.2, RN_FC.5
FC_ALT_MIN: A1.13, C_FC3.1, J_FC_ALT.3, RN_FC.4
FC_AZ_MAX: A1.12, C_FC2.1, J_FC_AZ.2, RN_FC.3
FC_AZ_MIN: A1.11, C_FC1.1, J_FC_AZ.3, RN_FC.2
GND: A1.4, A1.29, C_ALT.2, C_AZ.2, C_FC1.2, C_FC2.2, C_FC3.2, C_FC4.2, C_IN.2, C_VS.2, DRV_ALT_R.2, DRV_ALT_R.8, DRV_AZ_R.2, DRV_AZ_R.8, J_12V.2, J_12V.3, J_FC_ALT.1, J_FC_AZ.1, J_I2C.1, R_LED.2, R_VS2.2
JACK_IN: F_IN.1, J_12V.1
LED_ACT: A1.15, D_ACT.2
LED_K: D_ACT.1, R_LED.1
SCL: A1.24, J_I2C.4
SDA: A1.23, J_I2C.3
VIN_F: D_IN.2, F_IN.2
VM: A1.30, C_ALT.1, C_AZ.1, C_IN.1, DRV_ALT_R.1, DRV_AZ_R.1, D_IN.1, R_VS1.1
VM_SENSE: A1.19, C_VS.1, R_VS1.2, R_VS2.1

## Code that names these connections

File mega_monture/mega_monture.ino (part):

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static double         maxSlewRate   = DEFAULT_SLEW_RATE;

// === BROCHES ===
#define AZ_STEP   2
#define AZ_DIR    3
#define AZ_EN     4
#define BUZZER_PIN 49
#define BUZZ_FREQ  2000
#define ALT_STEP  5
#define ALT_DIR   6
#define ALT_EN    7

#define DEROT_STEP 8
#define DEROT_DIR  9
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  Serial3.begin(38400);                   
  Serial2.begin(9600);   // [ADD] Initialisation du port GPS

  pinMode(AZ_STEP,OUTPUT); pinMode(AZ_DIR,OUTPUT); pinMode(AZ_EN,OUTPUT);
  pinMode(ALT_STEP,OUTPUT);pinMode(ALT_DIR,OUTPUT);pinMode(ALT_EN,OUTPUT);
  pinMode(DEROT_STEP,OUTPUT); pinMode(DEROT_DIR,OUTPUT); pinMode(DEROT_EN,OUTPUT);
  pinMode(FOCUS_STEP,OUTPUT); pinMode(FOCUS_DIR,OUTPUT); pinMode(FOCUS_EN,OUTPUT);
  digitalWrite(DEROT_EN, HIGH);
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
